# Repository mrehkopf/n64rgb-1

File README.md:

# N64 RGB 

A collection of RGB mods for the N64. This repository includes:

- a simple RGB amp
  * based on TI's video amplifier THS7374 / THS7373 (only for some NTSC-units)
  * folder: simpleRGBAmp
- a general RGB digital-to-analog converter based on viletims schematics
  * supported devices: MaxII (EPM240T100C5, EPM570T100C5) and MaxV (5M240ZT100C4, 5M570ZT100C4) CPLDs
  * PCB files (common for all supported devices) and firmware (separate programming files) are provided
  * folder: generalRGBmod
- an advanced RGB digital-to-analog converter with optional YPbPr conversion
  * supported FPGA: Cyclone IV (EP4CE6E22 and EP4CE10E22) and Cyclone 10 LP (10CL006YE144 and 10CL010YE144)
  * PCB files (common for all supported devices) and firmware (separate programming files) are provided
  * additional Filter board for the outputted video signal if you need that
  * folder: advancedRGBmod
- additional MAV-NUS Adapter:
  * pin breakout from 0.8mm pitch to 1.27mm pitch
  * PCB files provided
  * folder: misc/MAV-NUS-BreakOut
- Filter AddOn for N64RGBv2 and N64 Advanced:
  * used to filter the video signal comming out of the ADV7125 or to adjust signal levels such that one can use SNES PAL RGB cables
  * PCB files provided
  * folder: misc/FilterAddOn
- an alternative firmware for viletims commercial N64 RGB modding kit
  * include in firmware folder of generalRGBmod
  * project: n64rgb_viletim.qpf

## Acknowledgement

Of course, many thanks to viletim for his initial CPLD-based DAC project, for providing a valuable commercial modding board as well as for publishing the schematics and source codes for that project.
I also want to send many thanks to Ikari_01. He has written the code to detect 480i and PAL/NTSC output with the CPLD. He provides a source code for the XC9572XL, which can be accessed here: [URL to Ikari_01's GitHub repository](https://github.com/mrehkopf/n64rgb)
Last but not least, thank you to Bob for his website [RetroRGB](http://retrorgb.com) and especially in this context here for collecting and sharing all the [RGB information regarding the N64](http://retrorgb.com/n64.html).

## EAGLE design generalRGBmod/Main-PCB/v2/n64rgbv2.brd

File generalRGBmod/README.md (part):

# General N64 RGB Digital-to-Analog Mod

This folder contains all you need for a complete DIY RGB mod.

Please don't ask me for selling a modding. I either sell some prototypes on some forums marketplaces (which is very unlikely) or I don't have any of the boards.
This is a complete DIY modding project. So everybody is on his own here.
If you are looking for a ready to install kit, just look on your own for a seller. Preferably you should invest your money into a [kit made by viletim](http://etim.net.au/shop/shop.php?crn=209). I also provide similar firmware files for his board in this GitHub repository, too.

**WARNING:** This is an advanced DIY project if you do everything on your own. You need decent soldering skills. The CPLD has 0.5mm fine pitch with 100pins. Next to it the video amp has a 0.65mm pin pitch on the board there are some SMD1206 resistor and ferrit bead arrays.

## Features

- Supporting for different CPLDs on a common PCB design:
  * MaxII EPM240T100C5
  * MaxII EPM570T100C5
  * MaxV 5M240ZT100C4 (a 5M240ZT100C5 does not met timing requirements [1])
  * MaxV 5M570ZT100C4 (a 5M570ZT100C5 does not met timing requirements [1])
- Video DAC:
  * V1: R2R ladder with video amplifier THS7374 or THS7373
  * V2: Video DAC ADV7125
- Detection of 240p/288p vs. 480i/576i together with detection of NTSC vs. PAL mode
- Heuristic for de-blur function [2], De-Blur in 240p/288p (horizontal resolution decreased from 640 to 320 pixels)
- 15bit color mode
- IGR features:
  * reset the console with the controller
  * full control on de-blur and 15bit mode with the controller
- Installation type: user decides whether he want to use IGR features or dedicated mechanical switches
- Slow Slew Rate
- for possibly future implementation: switch LPF of the video amplifier on and off (may only fit into CPLDs with 570LE)

The following shortly describes the main features of the firmware and how to use / control them.

#### Notes
##### [1]
Clocks are defined in the SDC-files place in the firmware folder.
The 5M240ZT100C5 and 5M570ZT100C5 does not met the timing requirements checked during the Timing Analysis. However, the default model is the so called *slow model*. If one uses the *fast model* for analysis, the timings are met without any problems.
So one could also give a try with the 5M240ZT100C5 or the 5M570ZT100C5, which should also works with 95% of all units produced in 'common' environments (e.g. living room temperature environment). Nevertheless, I won't garantee that.

Update: If you are looking for a 5M240ZT100C4 and 5M570ZT100C4, you propably realize that they are not in stock (e.g. at Mouser or Digikey). Then you can also use the 5M240ZT100I5 and 5M570ZT100I5, which are actually the same CPLDs.

##### [2]
Heuristic for de-blur function highly depends on the image content. So it might be the case that de-blur is switched on and off rapidly even on small content changes. In any case you can override the heuristic by forcing de-blur on or off.  
If you observe something like that or where do you think that de-blur is not correctly guessed, please take a note (PAL / NTSC N64, game, ROM, situation), where I can check that and can try to further improve the heuristic algorithm. Send me your observation vie email or open an issue here on GitHub.

### In-Game Routines (IGR) (default installation type)

Three functunalities are implemented: toggle de-blur feature / override heuristic for de-blur and toggle the 15bit mode (see above) as well as resetting the console.

The button combination are as follows:

- reset the console: Z + Start + R + A + B
- (de)activate de-blur / override heuristic for de-blur: (see description below)
- (de)activate 15bit mode: (see description below)

_Modifiying the IGR Button Combinations_:  
It's difficult to make everybody happy with it. Third party controllers, which differ from the original ones by design, make it even more difficult. So it is possible to generate your own firmware with **your own** preferred **button combinations** implemented. Please refere to the document **IGR.README.md** located in the top folder of this repository for further information.

_Final remark on IGR_:  
However, as the communication between N64 and the controller goes over a single wire, sniffing the input is not an easy task (and probably my solution is not the best one). This together with the lack of an exhaustive testing (many many games out there as well my limited time), I'm looking forward to any incomming issue report to furhter improve this feature :)

### De-Blur

De-blur of the picture information is only be done in 240p/288p. This is be done by simply blanking every second pixel. Normally, the blanked pixels are used to introduce blur by the N64 in 240p/288p mode. However, some games like Mario Tennis, 007 Goldeneye, and some others use these pixel for additional information rather than for bluring effects. In other words this means that these games uses full horizontal resolution even in 240p/288p output mode. Hence, the picture looks more blurry in this case if de-blur feature is activated.

- **By default heuristic is activated on every power cycle and on every reset!** However, as the heuristic guess might be not reliable, the guess can be override. Also, the heuristic algorithm can be switched off permanently by setting pin 2 of the CPLD to GND (short pin 1 and 2)
- Press Z + Start + R + C-le to deactivate de-blur (overrides the guess)
- Press Z + Start + R + C-ri to activate de-blur (overrides the guess)
- If heuristic estimation is switched off, the de-blur setting has a default value. This default is set on each power cycle but not on a reset. Default is de-blur *on*! If you want to have it *off* by default, short pin 91 and 90 at the CPLD!

_(Button combinations can be modified according to your needs - see note below @ **In-Game Routines (IGR)**)_

### Heuristic for De-Blur

As noted above, the N64 typically outputs a 320pixel wide picture in 240p/288p. As the pixel clock does not change compared to 480i/576i there outputted pixel wide is 640.
On the one hand, most games outputs a 320pixel wide picture in 240p/288p and use the remaining pixels to introduce a blur. This can be removed by simply blank these interpolated pixels.
On the other hand, a minor number of games outputs a 'full' 640pixel wide picture also in 240p/288p. In this case blanking out the suspected interpolated pixels causes a blurry picture.

The heuristic algorithm estimates whether a game uses the first or the second method. Depending on the result de-blur is active or not. However, as the estimation could be wrong, the user has the opportunity to override the estimation. (see section de-blur) At the moment it is not implemented that the heuristic can be switched on once overridden except with a reset or a new power cycle.

### 15bit Color Mode

The 15bit color mode reduces the color depth from 21bit (7bit for each color) downto 15bits (5bit for each color). Some very few games just use the five MSBs of the color information and the two LSBs for some kind of gamma dither. The 15bit color mode simply sets the two LSBs to '0'.

- By default the 15bit mode is *off*! The default is set on each power cycle but not on a reset. If you want to have it *on* by default, short pin 36 and 37 at the CPLD!
- to deactivate 15bit mode press Z + Start + R + C-up.
- to (re)activate 15bit mode press Z + Start + R + C-dw.

_(Button combinations can be modified according to your needs - see note below @ **In-Game Routines (IGR)**)_

### Jumpers - Altering Defaults and Installation Type

There are three jumpers jumpers on the modding board - one double solder jumper and one 'hidden' jumper - to set up deblur (IGR installation) and 15bit mode.  
The hidden jumper are nothing else then neighbouring pins. This pin is marked with an arrow. If you short a pair of pins you can change the default of the above noted features.  

- J11.1 -> deactivates de-blur by default (only applied if de-blur heuristic is off by default) **[1]**
- J11.2 -> deactivate the de-blur heuristic. **[1]**
- pin 36 and 37 (hidden jumper on v1) / J12.1 -> activates the 15bit color mode by default
- J12 (v1) / J12.2 (v2) -> Altering installation type **[2]** 

**Notes**:  

**[1]**  
Board Version September 2017 and later have a dedicated double solder jumper for de-blur heuristic and de-blur default. The jumper is labeled with _J11_ (left pad is _marked with a dot_). The middle pad is GND, the right pad is de-blur heuristic on (open) or off (short to middle) and the left pad is de-blur on (open) or off (short to middle), respectively.  
On older revisions _J11.1_ (pin 90 and 91) and _J11.2_ (pin 1 and 2) are hidden jumpers.  

**[2]**  
To use switches for de-blur (similar to viletims board) on can set the jumper _J12_ on the board. This deactivates the IGR functionalities and the user can use the in-/ouputs for controller and reset for switches.  
These switches are used as on viletims commercial board: **A**uto and **M**anual. The corresponding inputs are _Ctrl_ and _Rst#_, respectively. On newer boards (September 2017 and later) these pads are relabeled with _Ctrl/ A_ and _Rst#/ M_.

- If pad _Ctrl/ A_ is shorted to GND via a switch, the de-blur heuristic is used to switch de-blur on and off.
- If pad _Rst#/ M_ is shorted to GND via a switch, the de-blur is forced to be on (beats heuristic).

_J12_ is connected to pin 66 of the CPLD. Next to it is pin 65 which is connected to GND. If you have an older version of the board (August 2017 and earlier) running with the current firmware (September 2017 and later) you can short pin 65 and 66 to activate the alternative installation type.

### Slow Slew Rate

This feature reduces the rising and falling time of the outputs. This reduces artefacts due to fast rising/falling edges at the outputs and the resulting over-/undershoots. The drawback is that the edges are not as sharp as with fast slew rates (at least in theory), which is not noticeable.

### Low Pass Filter Bypass Mode of the THS7374 (v1 only)

The bypass mode of the internal filters is controlled by the CPLD. At the moment the CPLD forwards just the setting one can input to the CPLD over pad *Fil*.

- To leave the internal filters enabled you can left the pad open
- To bypass the filter set this pad to GND.

## Technical Information

A complete installation and setup guide to this modding kit is provided in the main folder of the repository. Here are some additional short notes.

### Checklist: How to build the project

- Use PCB files to order your own PCB or simply use the shared project on OSHPark
- Source the components you need, e.g. from Mouser
- Wait for everything to arrive
- Assemble your PCB (**N64RGBv1**):
  * If you use a MaxII CPLD, you have to assemble FB2 and must not use U3, C31 and C32.
  * If you use a MaxV CPLD, you need U3 (a 1.8V voltage regulator), C31 and C32. Don't touch FB2 in this case!
- Assemble your PCB (**N64RGBv2**):
  * If you use a MaxII CPLD, you have to assemble FB3 and must not use U4, C41 and C42.
  * If you use a MaxV CPLD, you need U4 (a 1.8V voltage regulator), C41 and C42. Don't touch FB3 in this case!
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
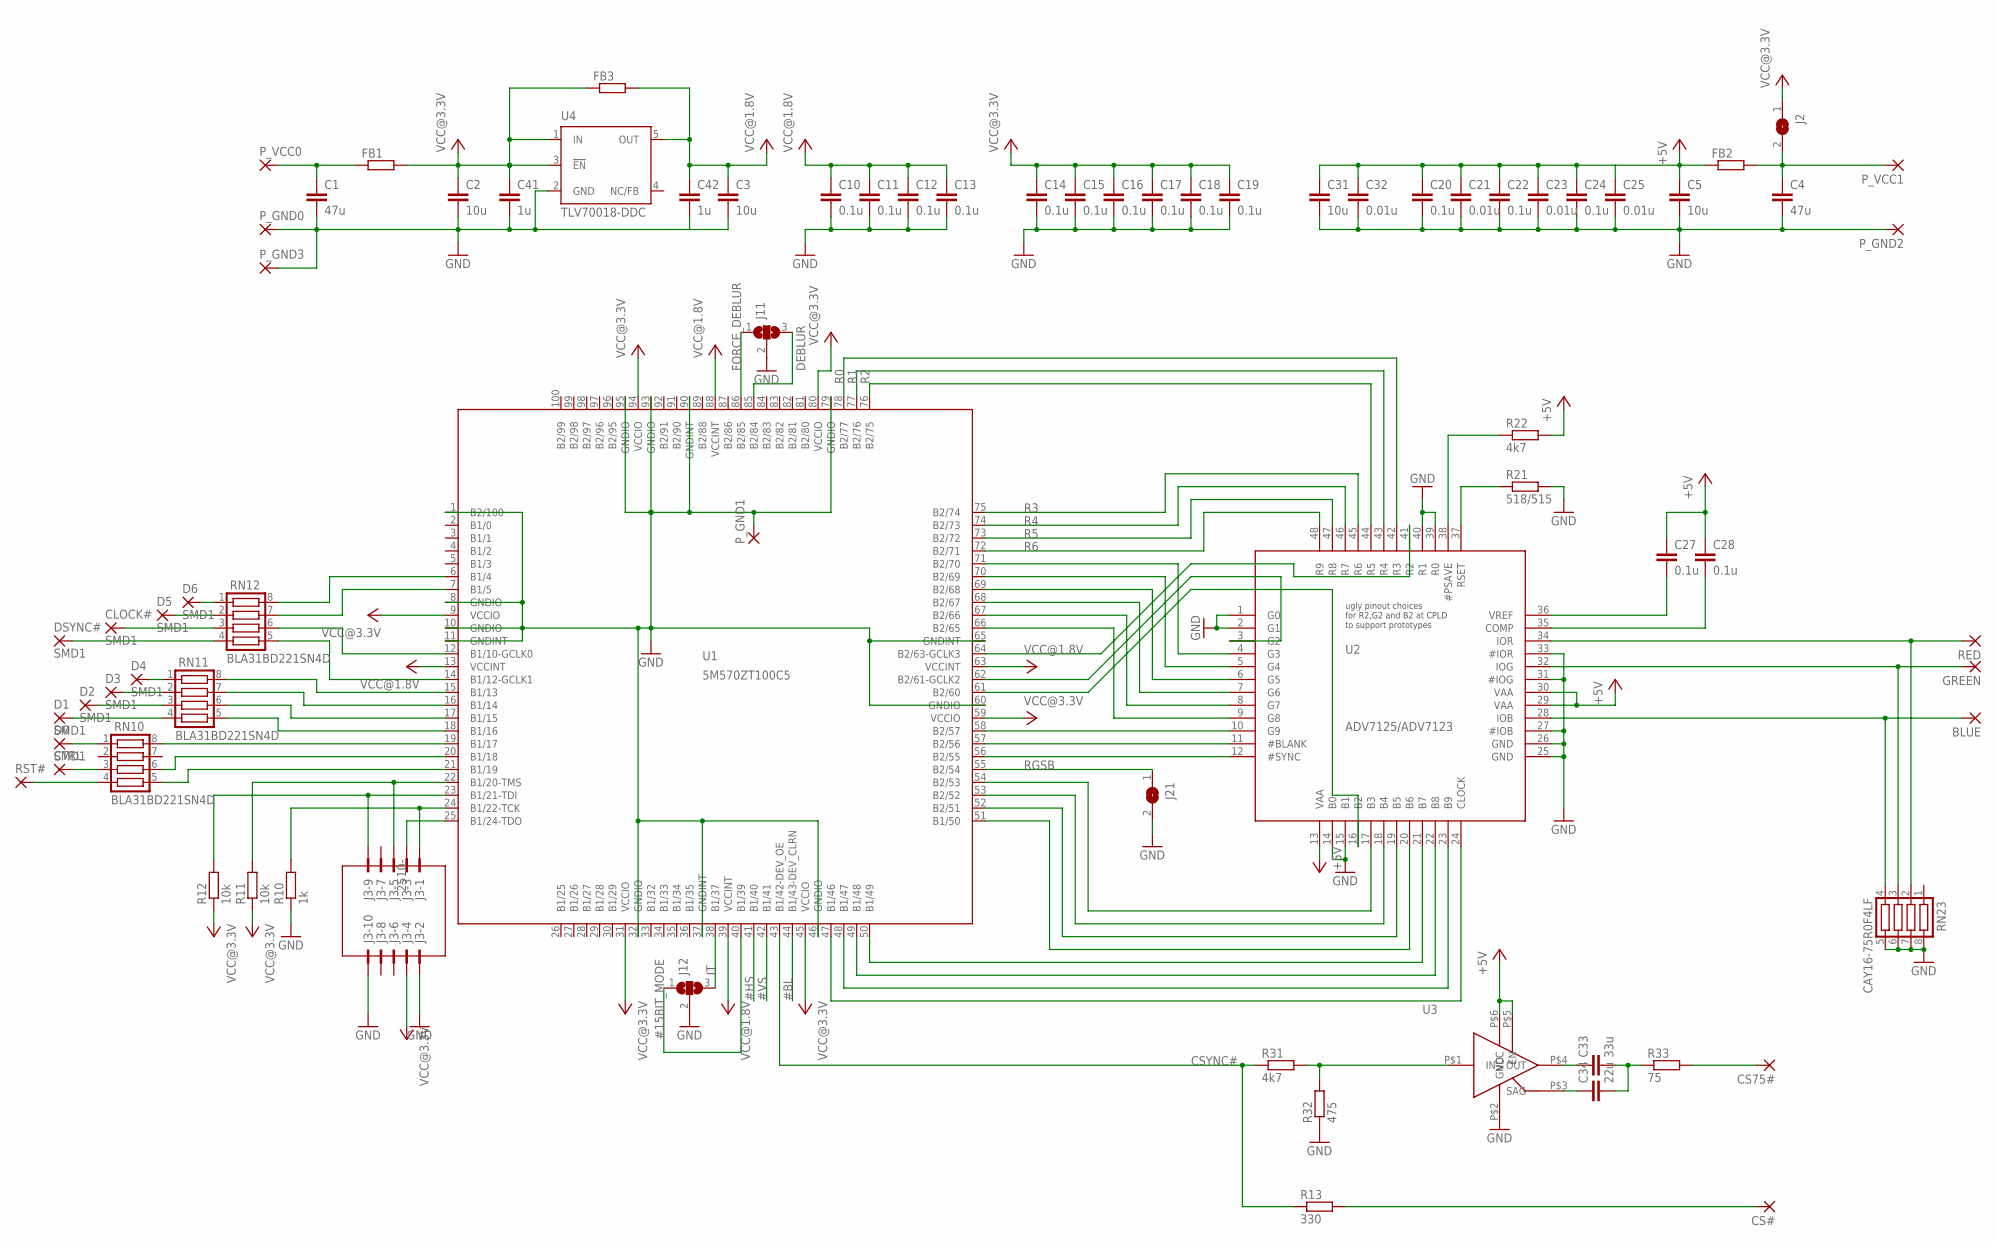
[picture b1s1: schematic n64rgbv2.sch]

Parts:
BLUE: SMD2; SMD1,27-2,54
C1, C4: 47u; C0805
C2, C3, C5, C31: 10u; C0805
C10, C11, C12, C13, C14, C15, C16, C17, C18, C19, C20, C22, C24, C27, C28: 0.1u; C0603
C21, C23, C25, C32: 0.01u; C0603
C33: 33u; C1210
C34: 22u; C1206
C41, C42: 1u; C0603
CLOCK#: SMD1; SMD0,8-1,6
CS75#: SMD2; SMD1,27-2,54
CS#: SMD2; SMD1,27-2,54
CTRL: SMD2; SMD1,27-2,54
D0, D1, D2, D3, D4, D5, D6: SMD1; SMD0,8-1,6
DSYNC#: SMD1; SMD0,8-1,6
FB1, FB2, FB3: R-EU_R0603; R0603
GREEN: SMD2; SMD1,27-2,54
J2, J21: SJ
J3: 2510-; PAK100/2500-10
J11, J12: SJ2W; SJ_2
P_GND0, P_GND1, P_GND2, P_GND3: SMD2; SMD1,27-2,54
P_VCC0, P_VCC1: SMD2; SMD1,27-2,54
R10: 1k; R0603
R11, R12: 10k; R0603
R13: 330; R0603
R21: 518/515; R0603
R22, R31: 4k7; R0603
R32: 475; R0603
R33: 75; R0603
RED: SMD2; SMD1,27-2,54
RN10, RN11, RN12: BLA31BD221SN4D; CTS742C083
RN23: CAY16-75R0F4LF; CTS742C083
RST#: SMD2; SMD1,27-2,54
U1: 5M570ZT100C5; TQFP100
U2: ADV7125/ADV7123; LQFP48
U3: TSH122ICT; SC70
U4: TLV70018-DDC; SOT23-DBV

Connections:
#15BIT_MODE: J12.1, U1.40 (B1/39)
#BL: U1.44 (B1/43-DEV_CLRN)
#HS: U1.41 (B1/40)
#VS: U1.42 (B1/41)
+5V: C5.1, C20.1, C21.1, C22.1, C23.1, C24.1, C25.1, C27.1, C28.1, C31.1, C32.1, FB2.1, R22.2, U2.13 (VAA), U2.29 (VAA), U2.30 (VAA), U3.P$5 (EN), U3.P$6 (VCC)
BLUE: BLUE.1, RN23.4, U2.28 (IOB)
CSYNC#: R13.1, R31.1, U1.43 (B1/42-DEV_OE)
DEBLUR: J11.3, U1.85 (B2/84)
FORCE_DEBLUR: J11.1, U1.86 (B2/85)
GND: C1.2, C2.2, C3.2, C4.2, C5.2, C10.2, C11.2, C12.2, C13.2, C14.2, C15.2, C16.2, C17.2, C18.2, C19.2, C20.2, C21.2, C22.2, C23.2, C24.2, C25.2, C31.2, C32.2, C41.2, C42.2, J3.2, J3.10, J11.2, J12.2, J21.2, P_GND0.1, P_GND1.1, P_GND2.1, P_GND3.1, R10.1, R21.2, R32.1, RN23.5, RN23.6, RN23.7, RN23.8, U1.1 (B2/100), U1.8 (GNDIO), U1.10 (GNDIO), U1.11 (GNDINT), U1.32 (GNDIO), U1.37 (GNDINT), U1.46 (GNDIO), U1.60 (GNDIO), U1.65 (GNDINT), U1.79 (GNDIO), U1.90 (GNDINT), U1.93 (GNDIO), U1.95 (GNDIO), U2.1 (G0), U2.2 (G1), U2.14 (B0), U2.15 (B1), U2.25 (GND), U2.26 (GND), U2.27 (#IOB), U2.31 (#IOG), U2.33 (#IOR), U2.39 (R0), U2.40 (R1), U3.P$2 (GND), U4.2 (GND)
GREEN: GREEN.1, RN23.3, U2.32 (IOG)
IT: J12.3, U1.38 (B1/37)
unnamed: D6.P$1, RN12.1
unnamed: D5.P$1, RN12.2
unnamed: DSYNC#.P$1, RN12.4
unnamed: CLOCK#.P$1, RN12.3
unnamed: RN10.4, RST#.1
unnamed: CTRL.1, RN10.3
unnamed: D0.P$1, RN10.1
unnamed: RN10.8, U1.19 (B1/17)
unnamed: RN10.6, U1.20 (B1/18)
unnamed: RN10.5, U1.21 (B1/19)
unnamed: RN11.5, U1.18 (B1/16)
unnamed: RN11.6, U1.17 (B1/15)
unnamed: CS#.1, R13.2
unnamed: RN11.7, U1.16 (B1/14)
unnamed: RN11.8, U1.15 (B1/13)
unnamed: D1.P$1, RN11.4
unnamed: D2.P$1, RN11.3
unnamed: D3.P$1, RN11.2
unnamed: D4.P$1, RN11.1
unnamed: RN12.7, U1.7 (B1/5)
unnamed: RN12.8, U1.6 (B1/4)
unnamed: RN12.5, U1.14 (B1/12-GCLK1)
unnamed: RN12.6, U1.12 (B1/10-GCLK0)
unnamed: U1.71 (B2/70), U2.4 (G3)
unnamed: U1.64 (B2/63-GCLK3), U2.41 (R2)
unnamed: U1.70 (B2/69), U2.5 (G4)
unnamed: U1.69 (B2/68), U2.6 (G5)
unnamed: U1.68 (B2/67), U2.7 (G6)
unnamed: U1.67 (B2/66), U2.8 (G7)
unnamed: U1.66 (B2/65), U2.9 (G8)
unnamed: U1.58 (B2/57), U2.10 (G9)
unnamed: U1.56 (B2/55), U2.12 (#SYNC)
unnamed: U1.47 (B1/46), U2.24 (CLOCK)
unnamed: U1.48 (B1/47), U2.23 (B9)
unnamed: U1.49 (B1/48), U2.22 (B8)
unnamed: U1.50 (B1/49), U2.21 (B7)
unnamed: U1.51 (B1/50), U2.20 (B6)
unnamed: U1.52 (B2/51), U2.19 (B5)
unnamed: U1.53 (B2/52), U2.18 (B4)
unnamed: U1.54 (B2/53), U2.17 (B3)
unnamed: U1.62 (B2/61-GCLK2), U2.3 (G2)
unnamed: U1.57 (B2/56), U2.11 (#BLANK)
unnamed: U1.61 (B2/60), U2.16 (B2)
unnamed: C4.1, FB2.2, J2.2, P_VCC1.1
unnamed: C1.1, FB1.1, P_VCC0.1
unnamed: C33.2, C34.2, R33.1
unnamed: CS75#.1, R33.2
unnamed: C33.1, U3.P$4 (OUT)
unnamed: C34.1, U3.P$3 (SAG)
unnamed: R21.1, U2.37 (RSET)
unnamed: R22.1, U2.38 (#PSAVE)
unnamed: C28.2, U2.35 (COMP)
unnamed: R31.2, R32.2, U3.P$1 (IN)
unnamed: C27.2, U2.36 (VREF)
R0: U1.78 (B2/77), U2.42 (R3)
R1: U1.77 (B2/76), U2.43 (R4)
R2: U1.76 (B2/75), U2.44 (R5)
R3: U1.75 (B2/74), U2.45 (R6)
R4: U1.74 (B2/73), U2.46 (R7)
R5: U1.73 (B2/72), U2.47 (R8)
R6: U1.72 (B2/71), U2.48 (R9)
RED: RED.1, RN23.2, U2.34 (IOR)
RGSB: J21.1, U1.55 (B2/54)
TCK: J3.1, R10.2, U1.24 (B1/22-TCK)
TDI: J3.9, R12.2, U1.23 (B1/21-TDI)
TDO: J3.3, U1.25 (B1/24-TDO)
TMS: J3.5, R11.2, U1.22 (B1/20-TMS)
VCC@3.3V: C2.1, C14.1, C15.1, C16.1, C17.1, C18.1, C19.1, C41.1, FB1.2, FB3.1, J2.1, J3.4, R11.1, R12.1, U1.9 (VCCIO), U1.31 (VCCIO), U1.45 (VCCIO), U1.59 (VCCIO), U1.80 (VCCIO), U1.94 (VCCIO), U4.1 (IN), U4.3 (!EN)

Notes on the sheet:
ugly pinout choices for R2,G2 and B2 at CPLD to support prototypes

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
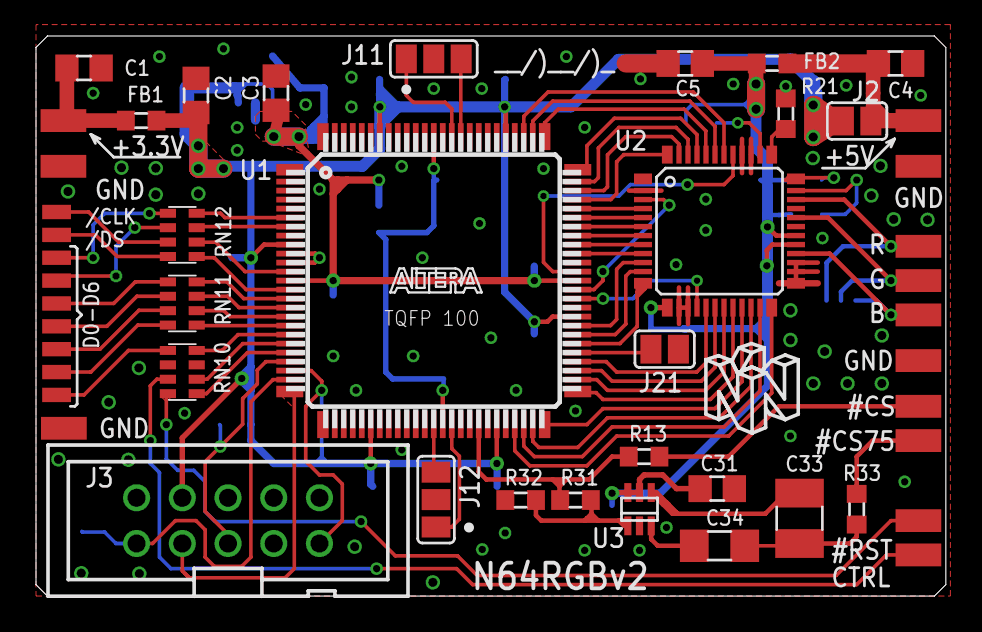
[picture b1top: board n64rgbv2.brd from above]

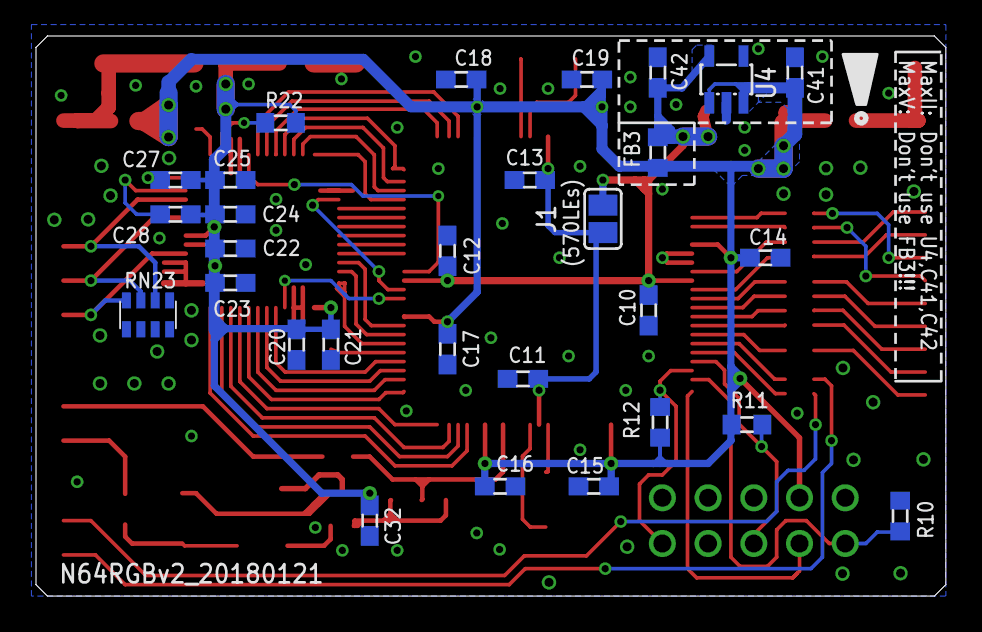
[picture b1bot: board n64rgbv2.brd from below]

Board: 2 copper layers, 50.5 x 31.1 mm, 77 parts (29 on the bottom side), 79 nets.

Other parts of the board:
J1: SJ

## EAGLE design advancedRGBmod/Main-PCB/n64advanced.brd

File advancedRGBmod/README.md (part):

# Advanced N64 RGB Digital-to-Analog Mod

This folder contains all you need for a complete DIY RGB mod.

Please don't ask me for selling a modding. I either sell some prototypes on some forums marketplaces (which is very unlikely) or I don't have any of the boards.
This is a complete DIY modding project. So everybody is on his own here.

**WARNING:** This is an advanced DIY project if you do everything on your own. You need decent soldering skills. The FPGA has 0.5mm fine pitch with 144pins and one exposed pad below the IC, which has to be soldered to the PCB. Next to it the video DAC has also 0.5mm pin pitch on the board there are some SMD1206 resistor and ferrit bead arrays.

## Features

- Supporting for different FPGAs [1] on a common PCB design:
  * (Cyclone IV EP4CE6E22)
  * Cyclone IV EP4CE10E22
  * (Cyclone 10 LP 10CL006YE144)
  * Cyclone 10 LP 10CL010YE144
- Video DAC ADV7125 (or ADV7123)
- Detection of 240p/288p vs. 480i/576i together with detection of NTSC vs. PAL mode
- Heuristic for de-blur function [2], De-Blur in 240p/288p (horizontal resolution decreased from 640 to 320 pixels)
- 15bit color mode
- IGR features:
  * reset the console with the controller
  * full control on de-blur and 15bit mode with the controller
- Advanced features:
  * output of RGsB or YPBPr on demand
  * linedoubling of 240p/288p video to 480p/576p [3]
  * selectable scanline strength: 0% (i.e. sl off), 25%, 50% and 100% [4]
  * optional bob de-interlace of 480i/576i to 480p/576p [3]
  * VGA output [5]

The following shortly describes the main features of the firmware and how to use / control them.

#### Notes
##### [1]
For now, all FPGAs seems to be fine. However, it might be the case that the 6k LEs FPGAs (EP4CE6E22 and 10CL006YE144) are to small for an OSD menu implementation due to the small amount of block RAM.

##### [2]
Heuristic for de-blur function highly depends on the image content. So it might be the case that de-blur is switched on and off rapidly even on small content changes. In any case you can override the heuristic by forcing de-blur on or off.  
If you observe something like that or where do you think that de-blur is not correctly guessed, please take a note (PAL / NTSC N64, game, ROM, situation), where I can check that and can try to further improve the heuristic algorithm. Send me your observation vie email or open an issue here on GitHub.

##### [3]
can be switched off

##### [4]
no scanlines are available in this mode

##### [5]
Not available if the filter adddon is used as HSYNC and VSYNC are shared outputs with F1 and F2 (filter selection)

### In-Game Routines (IGR)

Three functunalities are implemented: toggle de-blur feature / override heuristic for de-blur and toggle the 15bit mode (see above) as well as resetting the console.

The button combination are as follows:

- reset the console: Z + Start + R + A + B
- (de)activate de-blur / override heuristic for de-blur: (see description above)
- (de)activate 15bit mode: (see description above)

_Modifiying the IGR Button Combinations_:  
It's difficult to make everybody happy with it. Third party controllers, which differ from the original ones by design, make it even more difficult. So it is possible to generate your own firmware with **your own** preferred **button combinations** implemented. Please refere to the document **IGR.README.md** located in the top folder of this repository for further information.

_Final remark on IGR_:  
However, as the communication between N64 and the controller goes over a single wire, sniffing the input is not an easy task (and probably my solution is not the best one). This together with the lack of an exhaustive testing (many many games out there as well my limited time), I'm looking forward to any incomming issue report to furhter improve this feature :)

### De-Blur

De-blur of the picture information is only be done in 240p/288p. This is be done by simply blanking every second pixel. Normally, the blanked pixels are used to introduce blur by the N64 in 240p/288p mode. However, some games like Mario Tennis, 007 Goldeneye, and some others use these pixel for additional information rather than for bluring effects. In other words this means that these games uses full horizontal resolution even in 240p/288p output mode. Hence, the picture looks more blurry in this case if de-blur feature is activated.

- **By default heuristic is activated on every power cycle and on every reset!** However, as the heuristic guess might be not reliable, the guess can be overriden.
- Press Z + Start + R + C-le to deactivate de-blur (overrides the guess)
- Press Z + Start + R + C-ri to activate de-blur (overrides the guess)

_(Button combinations can be modified according to your needs - see note below @ **In-Game Routines (IGR)**)_

### Heuristic for De-Blur

As noted above, the N64 typically outputs a 320pixel wide picture in 240p/288p. As the pixel clock does not change compared to 480i/576i there outputted pixel wide is 640.
On the one hand, most games outputs a 320pixel wide picture in 240p/288p and use the remaining pixels to introduce a blur. This can be removed by simply blank these interpolated pixels.
On the other hand, a minor number of games outputs a 'full' 640pixel wide picture also in 240p/288p. In this case blanking out the suspected interpolated pixels causes a blurry picture.

The heuristic algorithm estimates whether a game uses the first or the second method. Depending on the result de-blur is active or not. However, as the estimation could be wrong, the user has the opportunity to override the estimation. (see section de-blur) At the moment it is not implemented that the heuristic can be switched on once overridden except with a reset or a new power cycle.

### 15bit Color Mode

The 15bit color mode reduces the color depth from 21bit (7bit for each color) downto 15bits (5bit for each color). Some very few games just use the five MSBs of the color information and the two LSBs for some kind of gamma dither. The 15bit color mode simply sets the two LSBs to '0'.

- By default the 15bit mode is *off*! The default is set on each power cycle but not on a reset.
- to deactivate 15bit mode press Z + Start + R + C-up.
- to (re)activate 15bit mode press Z + Start + R + C-dw.

_(Button combinations can be modified according to your needs - see note below @ **In-Game Routines (IGR)**)_

### Low Pass Filtering of the Video Output

The video DAC does not use any filtering. In general, this is also not needed. If you need DAC post-filtering though (receiver has a ADC build without any pre-filtering), you can install the filter addon (also provided in this repository).

The filter addon is based on a THS7368, where the video channels with selectable filter are used. As the filter is selected over the same pins as HSYNC and VSYNC, the addon is not compatible to VGA.

## Technical Information

A complete installation and setup guide to this modding kit is provided in the main folder of the repository. Here are some additional short notes.

### Checklist: How to build the project

- Use PCB files to order your own PCB or simply use the shared project(s) on OSHPark
- Source the components you need, e.g. from Mouser or Digikey
- Wait for everything to arrive
- Assemble your PCB
- Set all jumpers
- Flash the firmware to the serial flash device
  * You need a Altera USB Blaster
  * Use the JIC programming file if you want to program the serial flash over the FPGA or the SOF file if you have a AS programming adapter for the serial flash
  * The serial flash / board needs to be powered; so you may consider to install the PCB into your N64 first and then use the N64 for powering the board
  * If you want to build an adapter, you may take a look onto [my DIY adapter](https://oshpark.com/shared_projects/mEwjoesz) at [my profile on OSHPark](https://oshpark.com/profiles/borti4938)
- Install the modding board:
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
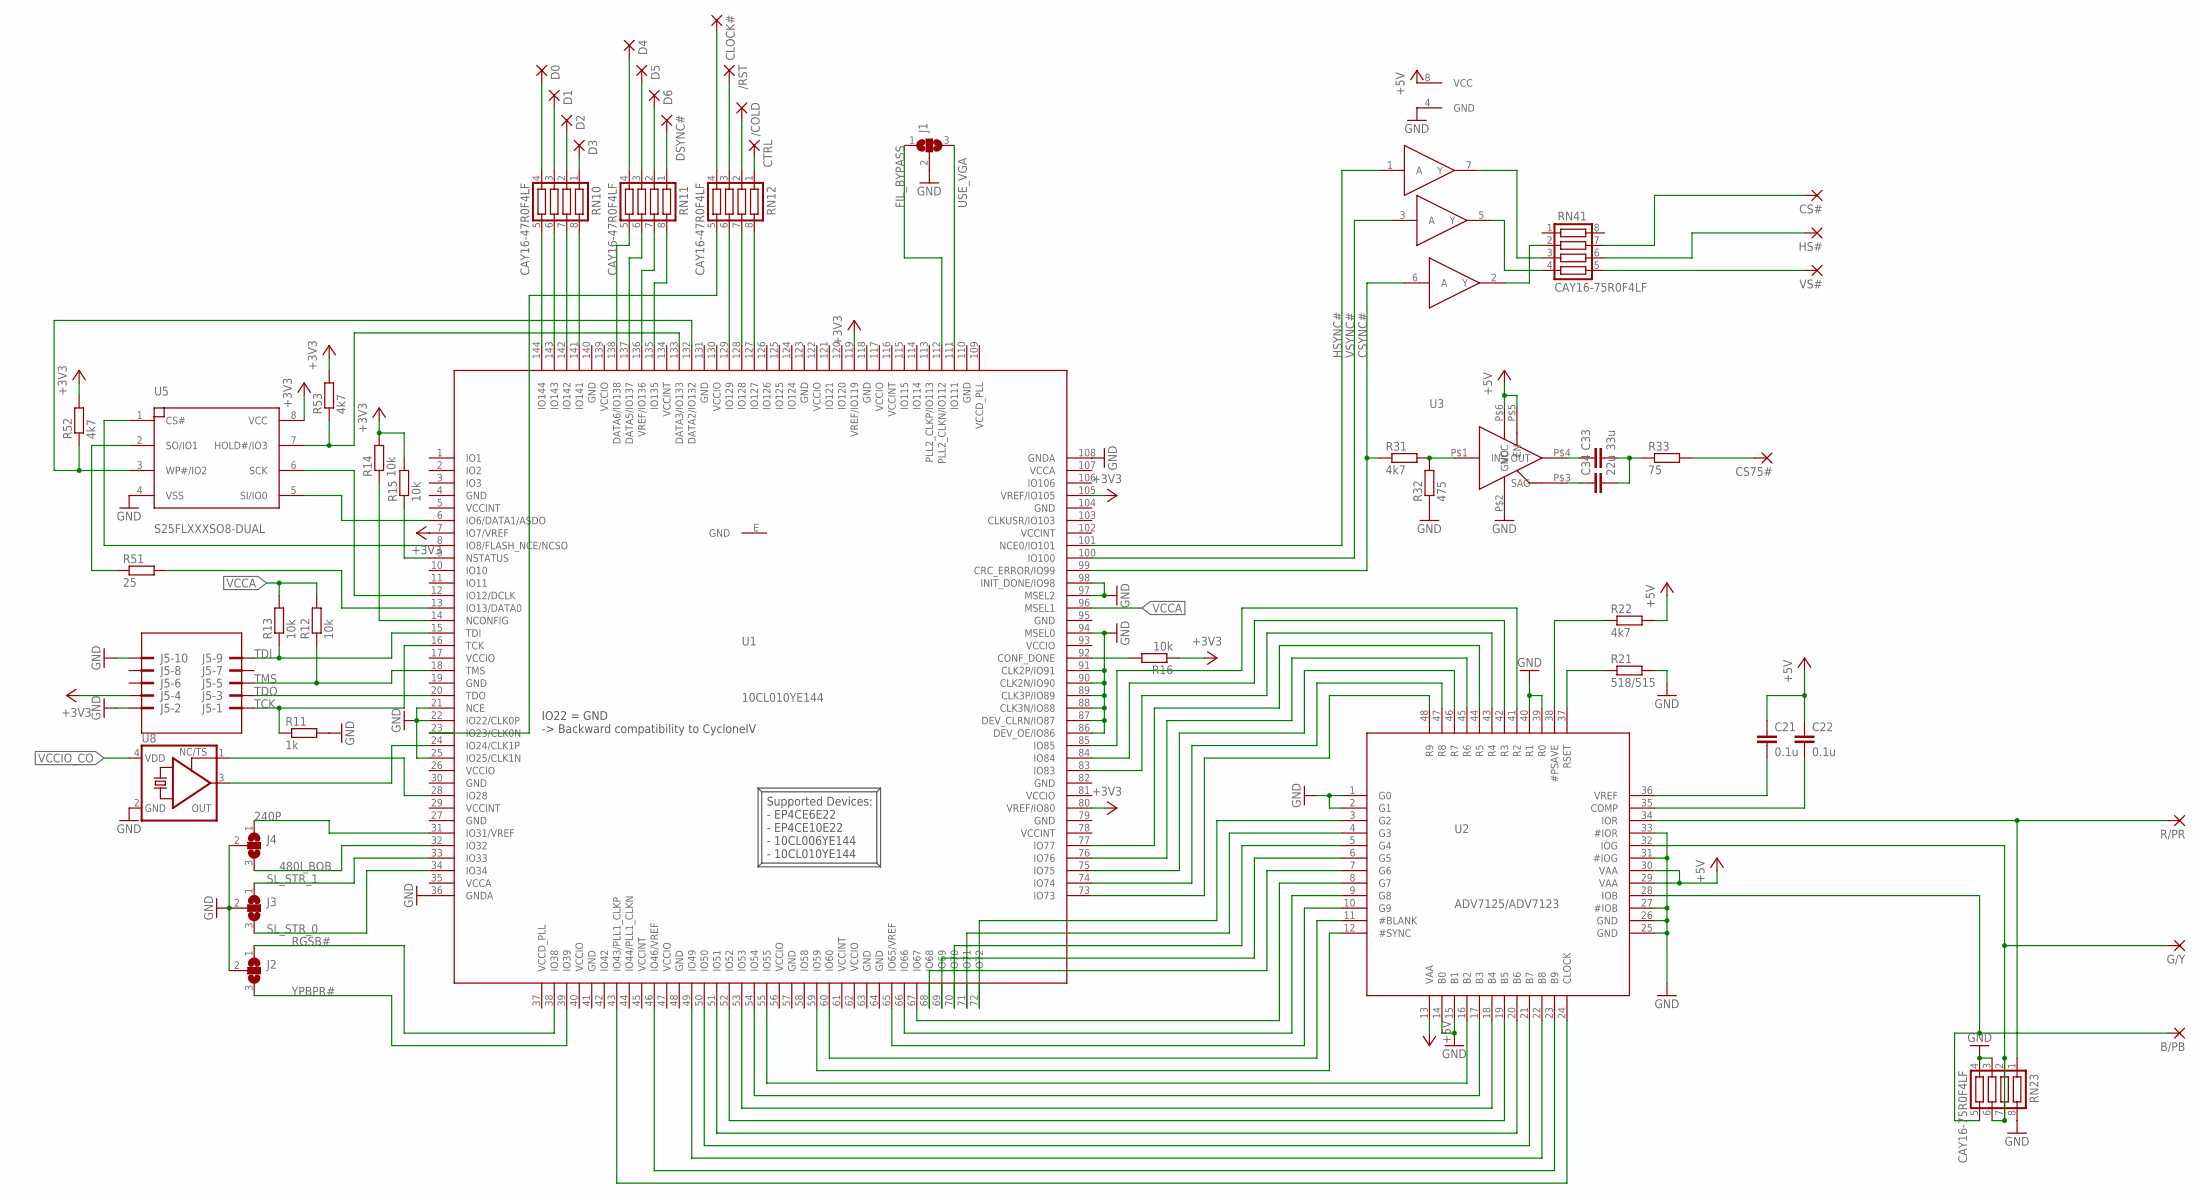
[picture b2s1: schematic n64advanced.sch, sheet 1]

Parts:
/COLD: SMD2; SMD1,27-2,54
/RST: SMD2; SMD1,27-2,54
B/PB: SMD2; SMD1,27-2,54
C21, C22: 0.1u; C0603
C33: 33u; C1210
C34: 22u; C1206
CLOCK#: SMD1; SMD0,8-1,6
CS75#: SMD2; SMD1,27-2,54
CS#: SMD2; SMD1,27-2,54
CTRL: SMD2; SMD1,27-2,54
D0, D1, D2, D3, D4, D5, D6: SMD1; SMD0,8-1,6
DSYNC#: SMD1; SMD0,8-1,6
G/Y: SMD2; SMD1,27-2,54
HS#: SMD2; SMD1,27-2,54
J1, J2, J3, J4: SJ2W; SJ_2
J5: 2510-; PAK100/2500-10
R11: 1k; R0603
R12, R13, R14, R15, R16: 10k; R0603
R21: 518/515; R0603
R22, R31, R52, R53: 4k7; R0603
R32: 475; R0603
R33: 75; R0603
R51: 25; R0603
R/PR: SMD2; SMD1,27-2,54
RN10, RN11, RN12: CAY16-47R0F4LF; CTS742C083
RN23, RN41: CAY16-75R0F4LF; CTS742C083
U1: 10CL010YE144; EQFP144_2
U2: ADV7125/ADV7123; LQFP48
U3: TSH122ICT; SC70
U4: 74LVC3G17; 74LVC3G34
U5: S25FLXXXSO8-DUAL; SO8-DUAL
U8: KXO-PXO/XO-V96; 3.2X2.5_KXO-V96
VS#: SMD2; SMD1,27-2,54

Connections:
240P: J4.1, U1.31 (IO31/VREF)
480I_BOB: J4.3, U1.32 (IO32)
+5V: C21.1, C22.1, R22.2, U2.13 (VAA), U2.29 (VAA), U2.30 (VAA), U3.P$5 (EN), U3.P$6 (VCC), U4.8 (VCC); also elsewhere on the board
BLUE: B/PB.1, RN23.5, U2.28 (IOB)
CSYNC47#: CS#.1, RN41.7
CSYNC#: R31.1, U1.99 (CRC_ERROR/IO99), U4.6 (A)
FIL_BYPASS: J1.1, U1.112 (PLL2_CLKN/IO112)
GND: J1.2, J2.2, J3.2, J4.2, J5.2, J5.10, R11.2, R21.2, R32.1, RN23.3, RN23.4, RN23.8, U1.4 (GND), U1.19 (GND), U1.21 (NCE), U1.22 (IO22/CLK0P), U1.25 (IO25/CLK1N), U1.27 (GND), U1.30 (GND), U1.36 (GNDA), U1.41 (GND), U1.48 (GND), U1.57 (GND), U1.63 (GND), U1.64 (GND), U1.79 (GND), U1.82 (GND), U1.86 (DEV_OE/IO86), U1.87 (DEV_CLRN/IO87), U1.88 (CLK3N/IO88), U1.89 (CLK3P/IO89), U1.90 (CLK2N/IO90), U1.91 (CLK2P/IO91), U1.94 (MSEL0), U1.95 (GND), U1.97 (MSEL2), U1.98 (INIT_DONE/IO98), U1.104 (GND), U1.108 (GNDA), U1.110 (GND), U1.118 (GND), U1.123 (GND), U1.131 (GND), U1.140 (GND), U1.E (GND), U2.1 (G0), U2.2 (G1), U2.14 (B0), U2.15 (B1), U2.25 (GND), U2.26 (GND), U2.27 (#IOB), U2.31 (#IOG), U2.33 (#IOR), U2.39 (R0), U2.40 (R1), U3.P$2 (GND), U4.4 (GND), U5.4 (VSS), U8.2 (GND); also elsewhere on the board
GREEN: G/Y.1, RN23.2, RN23.6, RN23.7, U2.32 (IOG)
HSYNC47#: HS#.1, RN41.6
HSYNC#: U1.101 (NCE0/IO101), U4.1 (A)
unnamed: R31.2, R32.2, U3.P$1 (IN)
unnamed: R21.1, U2.37 (RSET)
unnamed: RN12.5, U1.23 (IO23/CLK0N)
unnamed: U1.43 (IO43/PLL1_CLKP), U2.24 (CLOCK)
unnamed: U1.46 (IO46/VREF), U2.23 (B9)
unnamed: U1.49 (IO49), U2.22 (B8)
unnamed: U1.50 (IO50), U2.21 (B7)
unnamed: R14.1, U1.14 (NCONFIG)
unnamed: U1.51 (IO51), U2.20 (B6)
unnamed: U1.52 (IO52), U2.19 (B5)
unnamed: U1.53 (IO53), U2.18 (B4)
unnamed: U1.54 (IO54), U2.17 (B3)
unnamed: U1.55 (IO55), U2.16 (B2)
unnamed: U1.72 (IO72), U2.3 (G2)
unnamed: C33.1, U3.P$4 (OUT)
unnamed: C34.1, U3.P$3 (SAG)
unnamed: C33.2, C34.2, R33.1
unnamed: U1.71 (IO71), U2.4 (G3)
unnamed: U1.70 (IO70), U2.5 (G4)
unnamed: U1.69 (IO69), U2.6 (G5)
unnamed: CS75#.1, R33.2
unnamed: R22.1, U2.38 (#PSAVE)
unnamed: C22.2, U2.35 (COMP)
unnamed: C21.2, U2.36 (VREF)
unnamed: R52.1, U1.132 (DATA2/IO132), U5.3 (WP#/IO2)
unnamed: RN41.2, U4.2 (Y)
unnamed: U1.68 (IO68), U2.7 (G6)
unnamed: U1.67 (IO67), U2.8 (G7)
unnamed: U1.66 (IO66), U2.9 (G8)
unnamed: U1.65 (IO65/VREF), U2.10 (G9)
unnamed: U1.60 (IO60), U2.11 (#BLANK)
unnamed: U1.59 (IO59), U2.12 (#SYNC)
unnamed: U1.85 (IO85), U2.41 (R2)
unnamed: U1.84 (IO84), U2.42 (R3)
unnamed: U1.83 (IO83), U2.43 (R4)
unnamed: U1.77 (IO77), U2.44 (R5)
unnamed: U1.76 (IO76), U2.45 (R6)
unnamed: U1.75 (IO75), U2.46 (R7)
unnamed: U1.74 (IO74), U2.47 (R8)
unnamed: U1.73 (IO73), U2.48 (R9)
unnamed: RN10.5, U1.144 (IO144)
unnamed: RN10.6, U1.143 (IO143)
unnamed: RN10.7, U1.142 (IO142)
unnamed: RN10.8, U1.141 (IO141)
unnamed: R15.1, U1.9 (NSTATUS)
unnamed: RN11.5, U1.138 (DATA6/IO138)
unnamed: RN41.4, U4.5 (Y)
unnamed: RN11.6, U1.137 (DATA5/IO137)
unnamed: RN11.7, U1.136 (VREF/IO136)
unnamed: RN11.8, U1.135 (IO135)
unnamed: R16.2, U1.92 (CONF_DONE)
unnamed: D0.P$1, RN10.4
unnamed: RN12.6, U1.129 (IO129)
unnamed: RN12.7, U1.128 (IO128)
unnamed: RN12.8, U1.127 (IO127)
unnamed: D1.P$1, RN10.3
unnamed: D2.P$1, RN10.2
unnamed: D3.P$1, RN10.1
unnamed: D4.P$1, RN11.4
unnamed: D5.P$1, RN11.3
unnamed: D6.P$1, RN11.2
unnamed: DSYNC#.P$1, RN11.1
unnamed: CLOCK#.P$1, RN12.4
unnamed: CTRL.1, RN12.1
unnamed: /COLD.1, RN12.2
unnamed: RN41.3, U4.7 (Y)
unnamed: R51.1, U5.2 (SO/IO1)
unnamed: /RST.1, RN12.3
unnamed: R51.2, U1.13 (IO13/DATA0)
unnamed: U1.12 (IO12/DCLK), U5.6 (SCK)
unnamed: R53.1, U1.133 (DATA3/IO133), U5.7 (HOLD#/IO3)
unnamed: U1.8 (IO8/FLASH_NCE/NCSO), U5.1 (CS#)
unnamed: U1.6 (IO6/DATA1/ASDO), U5.5 (SI/IO0)
unnamed: U1.24 (IO24/CLK1P), U8.3 (OUT)
unnamed: U1.28 (IO28), U8.1 (TS)
RED: R/PR.1, RN23.1, U2.34 (IOR)
RGSB#: J2.1, U1.38 (IO38)
SL_STR_0: J3.3, U1.34 (IO34)
SL_STR_1: J3.1, U1.33 (IO33)
TCK: J5.1, R11.1, U1.16 (TCK)
TDI: J5.9, R13.1, U1.15 (TDI)
TDO: J5.3, U1.20 (TDO)
TMS: J5.5, R12.1, U1.18 (TMS)
USE_VGA: J1.3, U1.111 (IO111)
VCCA: R12.2, R13.2, U1.35 (VCCA), U1.96 (MSEL1), U1.107 (VCCA); also elsewhere on the board
VCCD_PLL: U1.37 (VCCD_PLL), U1.109 (VCCD_PLL); also elsewhere on the board
VCCINT: U1.5 (VCCINT), U1.29 (VCCINT), U1.45 (VCCINT), U1.61 (VCCINT), U1.78 (VCCINT), U1.102 (VCCINT), U1.116 (VCCINT), U1.134 (VCCINT); also elsewhere on the board
VCCIO: J5.4, R14.2, R15.2, R16.1, R52.2, R53.2, U1.7 (IO7/VREF), U1.17 (VCCIO), U1.26 (VCCIO), U1.40 (VCCIO), U1.47 (VCCIO), U1.56 (VCCIO), U1.62 (VCCIO), U1.80 (VREF/IO80), U1.81 (VCCIO), U1.93 (VCCIO), U1.105 (VREF/IO105), U1.117 (VCCIO), U1.119 (VREF/IO119), U1.122 (VCCIO), U1.130 (VCCIO), U1.139 (VCCIO), U5.8 (VCC); also elsewhere on the board
VCCIO_CO: U8.4 (VDD); also elsewhere on the board
VSYNC47#: RN41.5, VS#.1
VSYNC#: U1.100 (IO100), U4.3 (A)
YPBPR#: J2.3, U1.39 (IO39)

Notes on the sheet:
IO22 = GND -> Backward compatibility to CycloneIV
Supported Devices: - EP4CE6E22 - EP4CE10E22 - 10CL006YE144 - 10CL010YE144

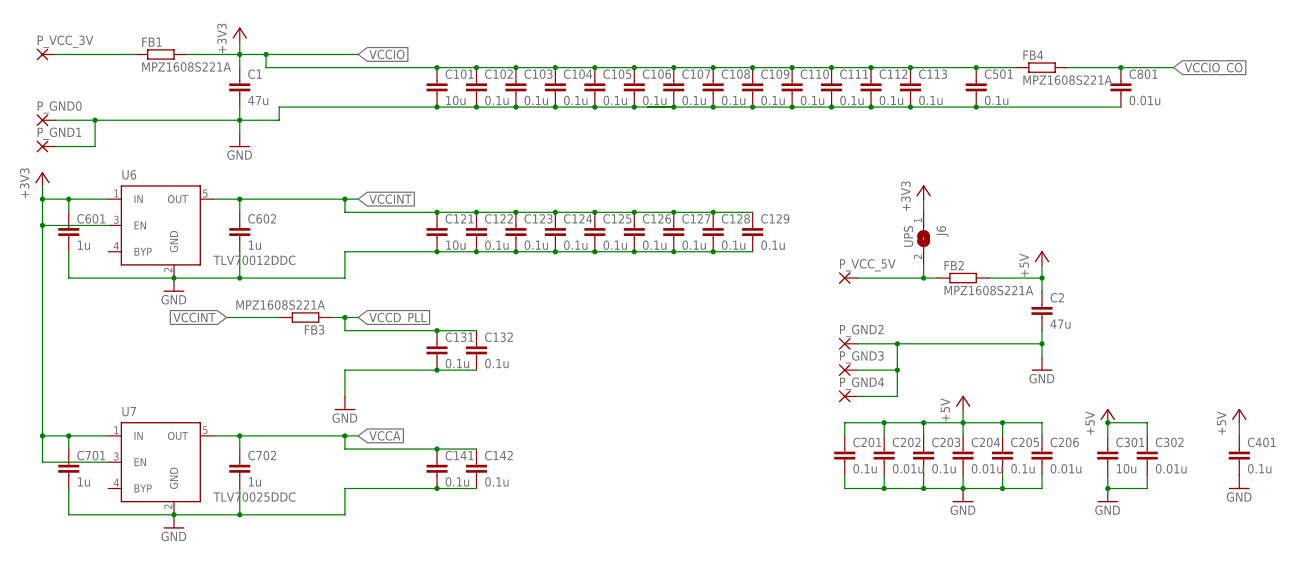
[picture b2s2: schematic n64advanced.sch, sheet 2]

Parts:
C1, C2: 47u; C0805
C101, C121, C301: 10u; C0805
C102, C103, C104, C105, C106, C107, C108, C109, C110, C111, C112, C113, C122, C123, C124, C125, C126, C127, C128, C129, C131, C132, C141, C142, C201, C203, C205, C401, C501: 0.1u; C0603
C202, C204, C206, C302, C801: 0.01u; C0603
C601, C602, C701, C702: 1u; C0603
FB1, FB2, FB3, FB4: MPZ1608S221A; R0603
J6: UPS; SJ
P_GND0, P_GND1, P_GND2, P_GND3, P_GND4: SMD2; SMD1,27-2,54
P_VCC_3V, P_VCC_5V: SMD2; SMD1,27-2,54
U6: TLV70012DDC; SOT23-5
U7: TLV70025DDC; SOT23-5

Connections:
+5V: C2.1, C201.1, C202.1, C203.1, C204.1, C205.1, C206.1, C301.1, C302.1, C401.1, FB2.2; also elsewhere on the board
GND: C1.2, C2.2, C101.2, C102.2, C103.2, C104.2, C105.2, C106.2, C107.2, C108.2, C109.2, C110.2, C111.2, C112.2, C113.2, C121.2, C122.2, C123.2, C124.2, C125.2, C126.2, C127.2, C128.2, C129.2, C131.2, C132.2, C141.2, C142.2, C201.2, C202.2, C203.2, C204.2, C205.2, C206.2, C301.2, C302.2, C401.2, C501.2, C601.2, C602.2, C701.2, C702.2, C801.2, P_GND0.1, P_GND1.1, P_GND2.1, P_GND3.1, P_GND4.1, U6.2 (GND), U7.2 (GND); also elsewhere on the board
unnamed: FB2.1, J6.2, P_VCC_5V.1
unnamed: FB1.1, P_VCC_3V.1
VCCA: C141.1, C142.1, C702.1, U7.5 (OUT); also elsewhere on the board
VCCD_PLL: C131.1, C132.1, FB3.1; also elsewhere on the board
VCCINT: C121.1, C122.1, C123.1, C124.1, C125.1, C126.1, C127.1, C128.1, C129.1, C602.1, FB3.2, U6.5 (OUT); also elsewhere on the board
VCCIO: C1.1, C101.1, C102.1, C103.1, C104.1, C105.1, C106.1, C107.1, C108.1, C109.1, C110.1, C111.1, C112.1, C113.1, C501.1, C601.1, C701.1, FB1.2, FB4.1, J6.1, U6.1 (IN), U6.3 (EN), U7.1 (IN), U7.3 (EN); also elsewhere on the board
VCCIO_CO: C801.1, FB4.2; also elsewhere on the board

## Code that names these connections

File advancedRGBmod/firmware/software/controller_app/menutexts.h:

/*********************************************************************************
 *
 * This file is part of the N64 RGB/YPbPr DAC project.
 *
 * Copyright (C) 2016-2018 by Peter Bartmann <borti4938@gmx.de>
 *
 * N64 RGB/YPbPr DAC is free software: you can redistribute it and/or modify
 * it under the terms of the GNU General Public License as published by
 * the Free Software Foundation, either version 3 of the License, or
 * any later version.
 *
 * This program is distributed in the hope that it will be useful,
 * but WITHOUT ANY WARRANTY; without even the implied warranty of
 * MERCHANTABILITY or FITNESS FOR A PARTICULAR PURPOSE.  See the
 * GNU General Public License for more details.
 *
 * You should have received a copy of the GNU General Public License
 * along with this program.  If not, see <http://www.gnu.org/licenses/>.
 *
 *********************************************************************************
 *
 * menutexts.h
 *
 *  Created on: 14.01.2018
 *      Author: Peter Bartmann
 *
 ********************************************************************************/

#ifndef MENUTEXTS_H_
#define MENUTEXTS_H_

#include <string.h>
#include <unistd.h>


#define HEADER_UNDERLINE      0x08
#define HOME_LOWSEC_UNDERLINE 0x01
#define HEADER_H_OFFSET       0
#define OVERLAY_V_OFFSET_WH   2
#define TEXTOVERLAY_H_OFFSET  0
#define HOMEOVERLAY_H_OFFSET  3

#define COPYRIGHT_SIGN          0x0A
#define COPYRIGHT_H_OFFSET      (VD_WIDTH - 15)
#define COPYRIGHT_V_OFFSET      (VD_HEIGHT - 1)
#define COPYRIGHT_SIGN_H_OFFSET (COPYRIGHT_H_OFFSET - 2)

#define CR_SIGN_LICENSE_H_OFFSET  15
#define CR_SIGN_LICENSE_V_OFFSET   2

#define VERSION_H_OFFSET 20
#define VERSION_V_OFFSET  5


#define BTN_OVERLAY_0_H_OFFSET  (VD_WIDTH - 12)
#define BTN_OVERLAY_0_V_OFFSET  (VD_HEIGHT - 4)
#define BTN_OVERLAY_1_H_OFFSET  (VD_WIDTH - 12)
#define BTN_OVERLAY_1_V_OFFSET  (VD_HEIGHT - 3)

#define CFG_OVERLAY_H_OFFSET  2
#define CFG_OVERLAY_V_OFFSET  OVERLAY_V_OFFSET_WH
#define CFG_VALS_H_OFFSET     (27 + CFG_OVERLAY_H_OFFSET)
#define CFG_VALS_V_OFFSET     CFG_OVERLAY_V_OFFSET
#define CFG_LINEX2_V_OFFSET   ( 1 + CFG_VALS_V_OFFSET)
#define CFG_480IBOB_V_OFFSET  ( 2 + CFG_VALS_V_OFFSET)
#define CFG_SLSTR_V_OFFSET    ( 3 + CFG_VALS_V_OFFSET)
#define CFG_FORMAT_V_OFFSET   ( 4 + CFG_VALS_V_OFFSET)
#define CFG_DEBLUR_V_OFFSET   ( 5 + CFG_VALS_V_OFFSET)
#define CFG_15BIT_V_OFFSET    ( 6 + CFG_VALS_V_OFFSET)
#define CFG_GAMMA_V_OFFSET    ( 7 + CFG_VALS_V_OFFSET)

#define MISC_OVERLAY_H_OFFSET   2
#define MISC_OVERLAY_V_OFFSET   OVERLAY_V_OFFSET_WH
#define MISC_VALS_H_OFFSET      (23 + MISC_OVERLAY_H_OFFSET)
#define MISC_VALS_V_OFFSET      CFG_OVERLAY_V_OFFSET
#define MISC_IGR_RESET_V_OFFSET ( 1 + MISC_VALS_V_OFFSET)
#define MISC_IGR_QUICK_V_OFFSET ( 2 + MISC_VALS_V_OFFSET)


#define INFO_OVERLAY_H_OFFSET 2
#define INFO_OVERLAY_V_OFFSET OVERLAY_V_OFFSET_WH
#define INFO_VALS_H_OFFSET    (18 + INFO_OVERLAY_H_OFFSET)
#define INFO_VALS_V_OFFSET    INFO_OVERLAY_V_OFFSET

#define INFO_VIN_V_OFFSET     (1 + INFO_VALS_V_OFFSET)
#define INFO_VOUT_V_OFFSET    (2 + INFO_VALS_V_OFFSET)
#define INFO_COL_V_OFFSET     (3 + INFO_VALS_V_OFFSET)
#define INFO_FORMAT_V_OFFSET  (4 + INFO_VALS_V_OFFSET)
#define INFO_DEBLUR_V_OFFSET  (5 + INFO_VALS_V_OFFSET)
#define INFO_FAO_V_OFFSET     (6 + INFO_VALS_V_OFFSET)


#define MAIN_OVERLAY_H_OFFSET 2
#define MAIN_OVERLAY_V_OFFSET OVERLAY_V_OFFSET_WH

#define MAIN2VINFO_V_OFFSET   (0 + MAIN_OVERLAY_V_OFFSET)
#define MAIN2CFG_V_OFFSET     (1 + MAIN_OVERLAY_V_OFFSET)
#define MAIN2MISC_V_OFFSET    (2 + MAIN_OVERLAY_V_OFFSET)
#define MAIN2SAVE_V_OFFSET    (3 + MAIN_OVERLAY_V_OFFSET)
#define MAIN2ABOUT_V_OFFSET   (5 + MAIN_OVERLAY_V_OFFSET)
#define MAIN2THANKS_V_OFFSET  (6 + MAIN_OVERLAY_V_OFFSET)
#define MAIN2LICENSE_V_OFFSET (7 + MAIN_OVERLAY_V_OFFSET)


static const char *copyright_note =
    "2018 borti4938"; /* 14 chars */

static const char *btn_overlay_0 =
    "A ... Enter\n"
    "B ... Close";

//static const char *btn_overlay_1 =
//    "B ... Back";

static const char *vinfo_header =
    "N64 Advanced - Video-Info";
static const char *vinfo_overlay =
    "* Video\n"
    "  - Input:\n"
    "  - Output:\n"
    "  - Color Depth:\n"
    "  - Format:\n"
    "* 240p-DeBlur:\n"
    "* Filter AddOn:";

static const char *cfg_header =
    "N64 Advanced - Configuration";
static const char *cfg_overlay =
    "* Linedoubling:\n"
    "  - LineX2:\n"
    "  - 480i de-int. (bob):\n"
    "  - Scanlines:\n"
    "* Output Format:\n"
    "* 240p-DeBlur:\n"
    "* 15bit Mode:\n"
    "* Gamma Value:";

static const char *misc_header =
    "N64 Advanced - Miscellaneous";
static const char *misc_overlay =
    "* In-Game Routines:\n"
    "  - Reset:\n"
    "  - Quick-Access:";

static const char *thanks_overlay =
    "The N64 RGB project would not be what it is\n"
    "without the contributions many other people.\n"
    "Here, I want to point out especially:\n"
    " - viletim  : First public DIY N64 DAC project\n"
    " - Ikari_01 : Initial implementation of PAL/NTSC\n"
    "              as well as 480i/576i detection\n"
    " - sftwninja: Pushing me to the N64A project\n"
    " - Xenogears: Sponsoring of prototypes\n\n"
    "Visit GitHub:\n"
    "     <https://github.com/borti4938/n64rgb>\n"
    "Any contribution in any kind is highly welcomed!";
  /* 123456789012345678901234567890123456789012345678 */

static const char *about_overlay =
    "The N64 RGB project is open source, i.e.\n"
    "PCB files, HDL and SW sources are provided\n"
    "to you FOR FREE!\n\n"
    "Your version\n"
    " - firmware (HDL):\n"
    " - firmware (SW) :\n\n"
    "Questions / Support:\n"
    " - GitHub: <https://github.com/borti4938/n64rgb>\n"
    " - Email:  <borti4938@gmx.de>";
  /* 123456789012345678901234567890123456789012345678 */

static const char *license_overlay =
    "The N64Advanced is part of the\n"
    "N64 RGB/YPbPr DAC project\n"
    "     Copyright   2015 - 2018 Peter Bartmann\n"
    "This project is published under GNU GPL v3.0 or\n"
    "later. You should have received a copy of the\n"
    "GNU General Public License along with this\n"
    "project. If not, see \n"
    "      <http://www.gnu.org/licenses/>.\n\n"
    "What ever you do, also respect licenses of third\n"
    "party vendors providing the design tools...";
  /* 123456789012345678901234567890123456789012345678  */

static const char *home_header =
    "N64 Advanced - Main Menu";
static const char *home_overlay =
    "[Video-Info]\n"
    "[Configuration]\n"
    "[Miscellaneous]\n"
    "[Load/Save]\n\n"
    "About...\n"
    "Acknowledgment...\n"
    "License...";


const char *OffOn[]        = {"Off","On"};
const char *VideoMode[]    = {"240p60","288p50","480i60","576i50","480p60","576p50"};
const char *VideoColor[]   = {"21bit","15bit"};
const char *VideoFormat[]  = {"RGBS","RGBS/RGsB","YPbPr"};
const char *DeBlur[]       = {"(estimated)","(forced)","(480i/576i)"};
const char *DeBlurCfg[]    = {"Auto","Off","Always"};
const char *FilterAddOn[]  = {"not installed","9.5MHz","18MHz","Filter bypassed"};
const char *SLStrength[]   = {"0%","25%","50%","100%"};
const char *GammaValue[]   = {"0.70","0.75","0.80","0.85","0.90","1.00","1.10","1.15","1.20"};
const char *QuickChange[]  = {"Off","DeBlur","15bit mode","All"};

#endif /* MENUTEXTS_H_ */

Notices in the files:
parts and their libraries:
crystal-geyer_V1_0: Copyright: Geyer-Electronic
